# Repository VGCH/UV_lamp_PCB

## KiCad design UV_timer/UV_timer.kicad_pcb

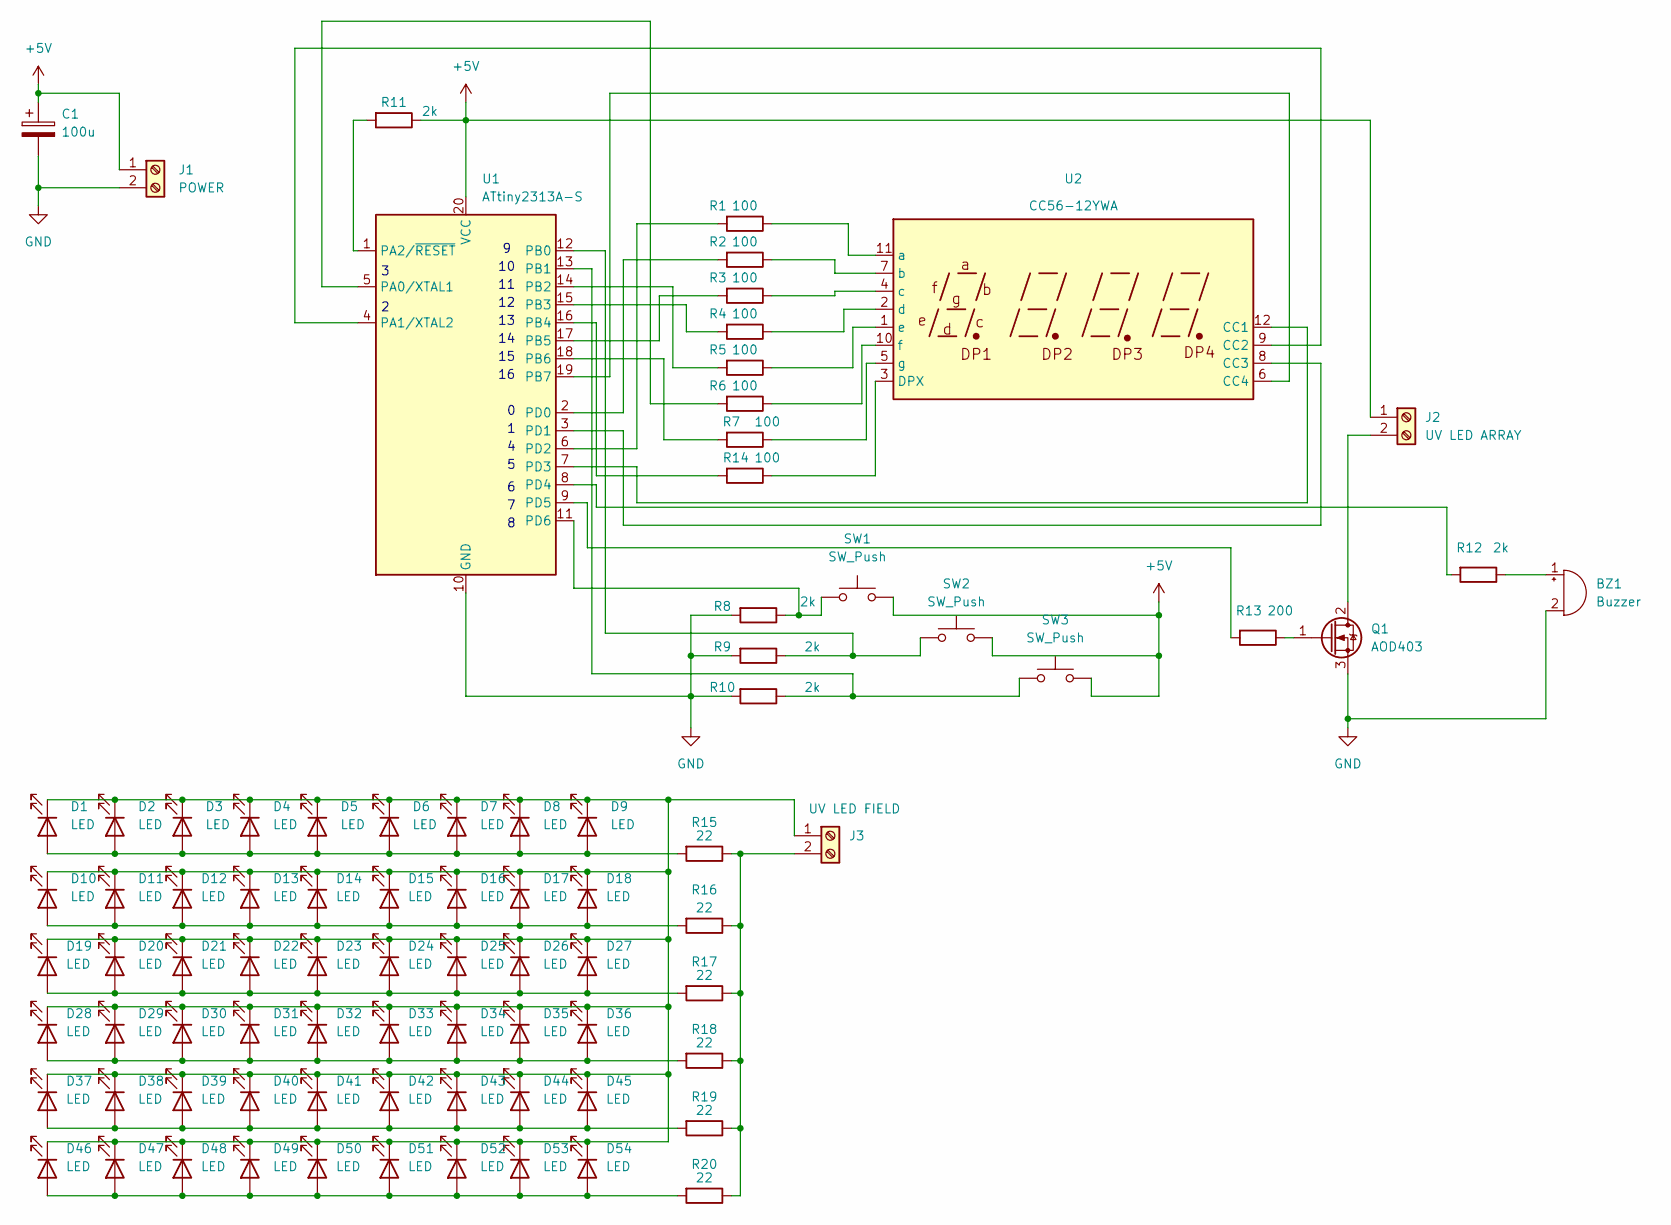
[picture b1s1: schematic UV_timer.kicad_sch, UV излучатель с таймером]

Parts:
BZ1: Buzzer; Buzzer_12x9.5RM7.6
C1: 100u; CP_Elec_6.3x5.4_Nichicon
D1, D2, D3, D4, D5, D6, D7, D8, D9, D10, D11, D12, D13, D14, D15, D16, D17, D18, D19, D20, D21, D22, D23, D24, D25, D26, D27, D28, D29, D30, D31, D32, D33, D34, D35, D36, D37, D38, D39, D40, D41, D42, D43, D44, D45, D46, D47, D48, D49, D50, D51, D52, D53, D54: LED; LED_D5.0mm
J1: POWER; TerminalBlock_bornier-2_P5.08mm
J2: UV LED ARRAY; TerminalBlock_bornier-2_P5.08mm
J3: UV LED FIELD; TerminalBlock_bornier-2_P5.08mm
Q1: AOD403; TO-252-2
R1, R2, R3, R4, R5, R6, R7, R14: 100; R_0805_2012Metric
R8, R9, R10, R11, R12: 2k; R_0805_2012Metric
R13: 200; R_0805_2012Metric
R15, R16, R17, R18, R19, R20: 22; R_0805_2012Metric
SW1, SW2, SW3: SW_Push; SW_PUSH_6mm
U1: ATtiny2313A-S; SOIC-20W_7.5x12.8mm_P1.27mm
U2: CC56-12YWA

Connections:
+5V: C1.1, J1.1, J2.1, R11.1, SW1.2, SW2.2, SW3.2, U1.20 (VCC)
GND: BZ1.2 (+), C1.2, J1.2, Q1.3 (S), R8.2, R9.2, R10.2, U1.10 (GND)
unnamed: BZ1.1 (-), R12.1
unnamed: D1.2 (A), D2.2 (A), D3.2 (A), D4.2 (A), D5.2 (A), D6.2 (A), D7.2 (A), D8.2 (A), D9.2 (A), R15.2
unnamed: D1.1 (K), D2.1 (K), D3.1 (K), D4.1 (K), D5.1 (K), D6.1 (K), D7.1 (K), D8.1 (K), D9.1 (K), D10.1 (K), D11.1 (K), D12.1 (K), D13.1 (K), D14.1 (K), D15.1 (K), D16.1 (K), D17.1 (K), D18.1 (K), D19.1 (K), D20.1 (K), D21.1 (K), D22.1 (K), D23.1 (K), D24.1 (K), D25.1 (K), D26.1 (K), D27.1 (K), D28.1 (K), D29.1 (K), D30.1 (K), D31.1 (K), D32.1 (K), D33.1 (K), D34.1 (K), D35.1 (K), D36.1 (K), D37.1 (K), D38.1 (K), D39.1 (K), D40.1 (K), D41.1 (K), D42.1 (K), D43.1 (K), D44.1 (K), D45.1 (K), D46.1 (K), D47.1 (K), D48.1 (K), D49.1 (K), D50.1 (K), D51.1 (K), D52.1 (K), D53.1 (K), D54.1 (K), J3.1
unnamed: D10.2 (A), D11.2 (A), D12.2 (A), D13.2 (A), D14.2 (A), D15.2 (A), D16.2 (A), D17.2 (A), D18.2 (A), R16.2
unnamed: D19.2 (A), D20.2 (A), D21.2 (A), D22.2 (A), D23.2 (A), D24.2 (A), D25.2 (A), D26.2 (A), D27.2 (A), R17.2
unnamed: D28.2 (A), D29.2 (A), D30.2 (A), D31.2 (A), D32.2 (A), D33.2 (A), D34.2 (A), D35.2 (A), D36.2 (A), R18.2
unnamed: D37.2 (A), D38.2 (A), D39.2 (A), D40.2 (A), D41.2 (A), D42.2 (A), D43.2 (A), D44.2 (A), D45.2 (A), R19.2
unnamed: D46.2 (A), D47.2 (A), D48.2 (A), D49.2 (A), D50.2 (A), D51.2 (A), D52.2 (A), D53.2 (A), D54.2 (A), R20.2
unnamed: J2.2, Q1.2 (D)
unnamed: J3.2, R15.1, R16.1, R17.1, R18.1, R19.1, R20.1
unnamed: Q1.1 (G), R13.1
unnamed: R6.2, U1.5 (PA0/XTAL1)
unnamed: U1.4 (PA1/XTAL2), U2.9 (CC2)
unnamed: R11.2, U1.1 (PA2/~RESET)
unnamed: R9.1, SW2.1, U1.12 (PB0)
unnamed: R10.1, SW3.1, U1.13 (PB1)
unnamed: R5.2, U1.14 (PB2)
unnamed: R4.2, U1.15 (PB3)
unnamed: R14.2, U1.16 (PB4)
unnamed: R3.2, U1.17 (PB5)
unnamed: R7.2, U1.18 (PB6)
unnamed: U1.19 (PB7), U2.6 (CC4)
unnamed: R2.2, U1.2 (PD0)
unnamed: U1.3 (PD1), U2.8 (CC3)
unnamed: R1.2, U1.6 (PD2)
unnamed: U1.7 (PD3), U2.12 (CC1)
unnamed: R12.2, U1.8 (PD4)
unnamed: R13.2, U1.9 (PD5)
unnamed: R8.1, SW1.1, U1.11 (PD6)
unnamed: R14.1, U2.3 (DPX)
unnamed: R1.1, U2.11 (a)
unnamed: R2.1, U2.7 (b)
unnamed: R3.1, U2.4 (c)
unnamed: R4.1, U2.2 (d)
unnamed: R5.1, U2.1 (e)
unnamed: R6.1, U2.10 (f)
unnamed: R7.1, U2.5 (g)

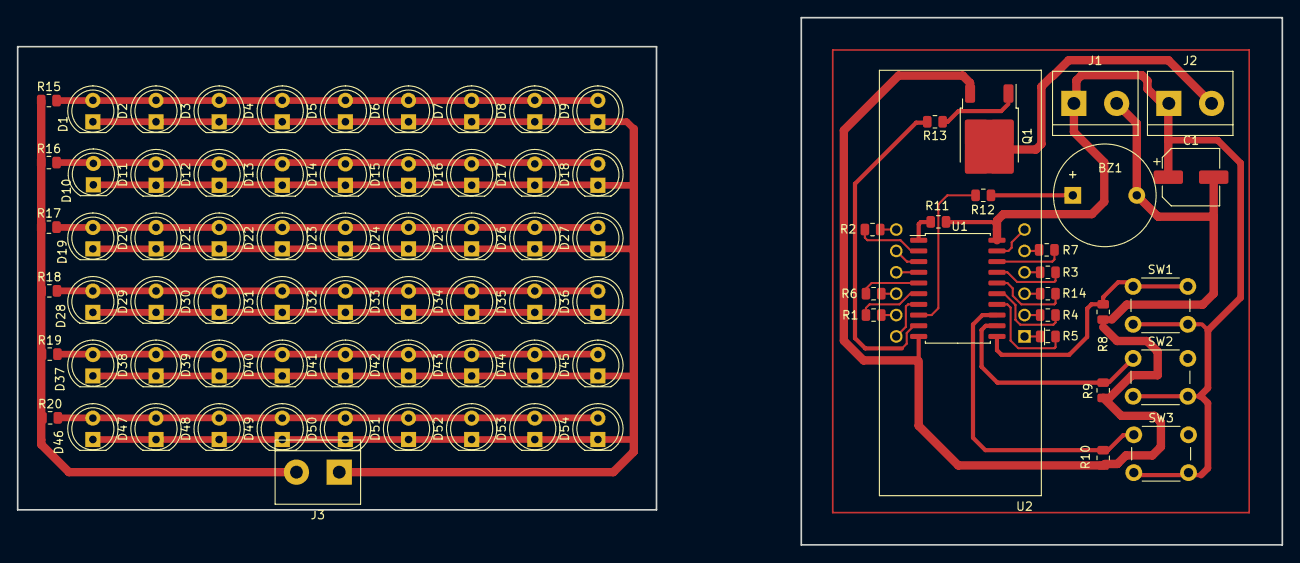
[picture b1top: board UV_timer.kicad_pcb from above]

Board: 2 copper layers, 150.2 x 62.6 mm, 85 parts (0 on the bottom side), 39 nets.
